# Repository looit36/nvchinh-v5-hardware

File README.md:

# MiniChinh - Micromouse Robot Controller Board

Dự án thiết kế mạch điều khiển robot dò mê cung (Micromouse) sử dụng phần mềm **KiCad**. Mạch tích hợp vi điều khiển STM32F411 tốc độ cao, driver động cơ kép, cảm biến quán tính IMU 6 trục, cảm biến encoder từ tính và dàn cảm biến quang hồng ngoại (IR).

---

## Hình ảnh Mạch PCB (3D & 2D Layout)

### Phối cảnh 3D

| Mặt trên | Mặt dưới |
| :---: | :---: |
|  |  |

| F.Cu + Silk | B.Cu + Silk |
| :---: | :---: |
|  |  |

---

## Sơ đồ Nguyên lý

### 1. Sơ đồ khối chính

### 2. Sơ đồ mạch phát & thu hồng ngoại

---

## Thông số Kỹ thuật Phần cứng

| Thành phần | Chi tiết linh kiện | Chức năng |
| :--- | :--- | :--- |
| **Vi điều khiển (MCU)** | STM32F411CEU6 (UFQFPN-48) | ARM Cortex-M4 100MHz, 512KB Flash, 128KB SRAM |
| **Driver Động cơ** | TI DRV8833PW (HTSSOP-16) | Điều khiển 2 động cơ DC độc lập, dòng tối đa 1.5A/kênh |
| **Cảm biến góc (IMU)** | Bosch BMI160 (LGA-14) | Cảm biến gia tốc & con quay hồi chuyển 6 trục (SPI/I2C) |
| **Bộ mã hóa bánh xe (Encoder)** | 2x MT6701CT (SO-8) | Cảm biến góc từ tính độ chính xác cao cho 2 bánh xe |
| **Cảm biến khoảng cách / Mê cung** | 4x SFH4546 (IR LED) + 4x SFH300 (Phototransistor) | Đo khoảng cách các vách tường mê cung, lái bằng MOSFET AO3400A |
| **Mạch nguồn (Power)** | AMS1117-5.0 & TI TPS73633DBV | Ổn áp 5V và 3.3V Low-Dropout cấp nguồn ổn định cho MCU và cảm biến |
| **Giao tiếp lập trình** | Cổng SWD chuẩn (GND, 3V3, SWDIO, SWCLK) | Nạp và gỡ lỗi bằng ST-Link / J-Link |
| **Ngoại vi & UI** | 5x LED báo trạng thái SMD 0603, 2x nút nhấn, 1x công tắc nguồn MSK12C02 | Giao diện tương tác và chọn chế độ chạy |

---

## Cấu trúc Thư mục

```text
minichinh/
├── minichinh.kicad_pro       # File dự án KiCad chính
├── minichinh.kicad_sch       # Sơ đồ nguyên lý chính
├── iremitter.kicad_sch       # Sơ đồ nguyên lý khối IR Emitter
├── minichinh.kicad_pcb       # Bản vẽ thiết kế mạch in PCB
├── fp-lib-table              # Bảng thư viện footprint
├── mouse.pretty/             # Thư viện footprint tùy chỉnh cho robot
├── minichinh.csv             # Danh sách bảng linh kiện (BOM)
├── geber/                    # Bộ file Gerber sẵn sàng để đặt mạch gia công
├── images/                   # Hình ảnh sơ đồ schematic và render 3D / 2D PCB
│   ├── minichinh.svg
│   ├── minichinh_ir_emitter.svg
│   ├── minichinh_schematic.pdf
│   ├── pcb_3d_top.png
│   ├── pcb_3d_bottom.png
│   ├── pcb_3d_iso.png
│   ├── pcb_top_layout.svg
│   └── pcb_bottom_layout.svg
└── README.md                 # Tài liệu giới thiệu dự án
```

---

## Hướng dẫn Sử dụng

1. **Mở dự án:**
   - Cài đặt KiCad phiên bản 8.0 hoặc 9.0 trở lên.
   - Mở file `minichinh.kicad_pro` để truy cập sơ đồ nguyên lý và layout PCB.
2. **Gia công mạch (PCB Manufacturing):**
   - Bộ file Gerber nén và đầy đủ các lớp đã được tạo sẵn trong thư mục [`geber/`](geber/). Có thể gửi trực tiếp cho các nhà sản xuất PCB (JLCPCB, PCBWay, v.v.).

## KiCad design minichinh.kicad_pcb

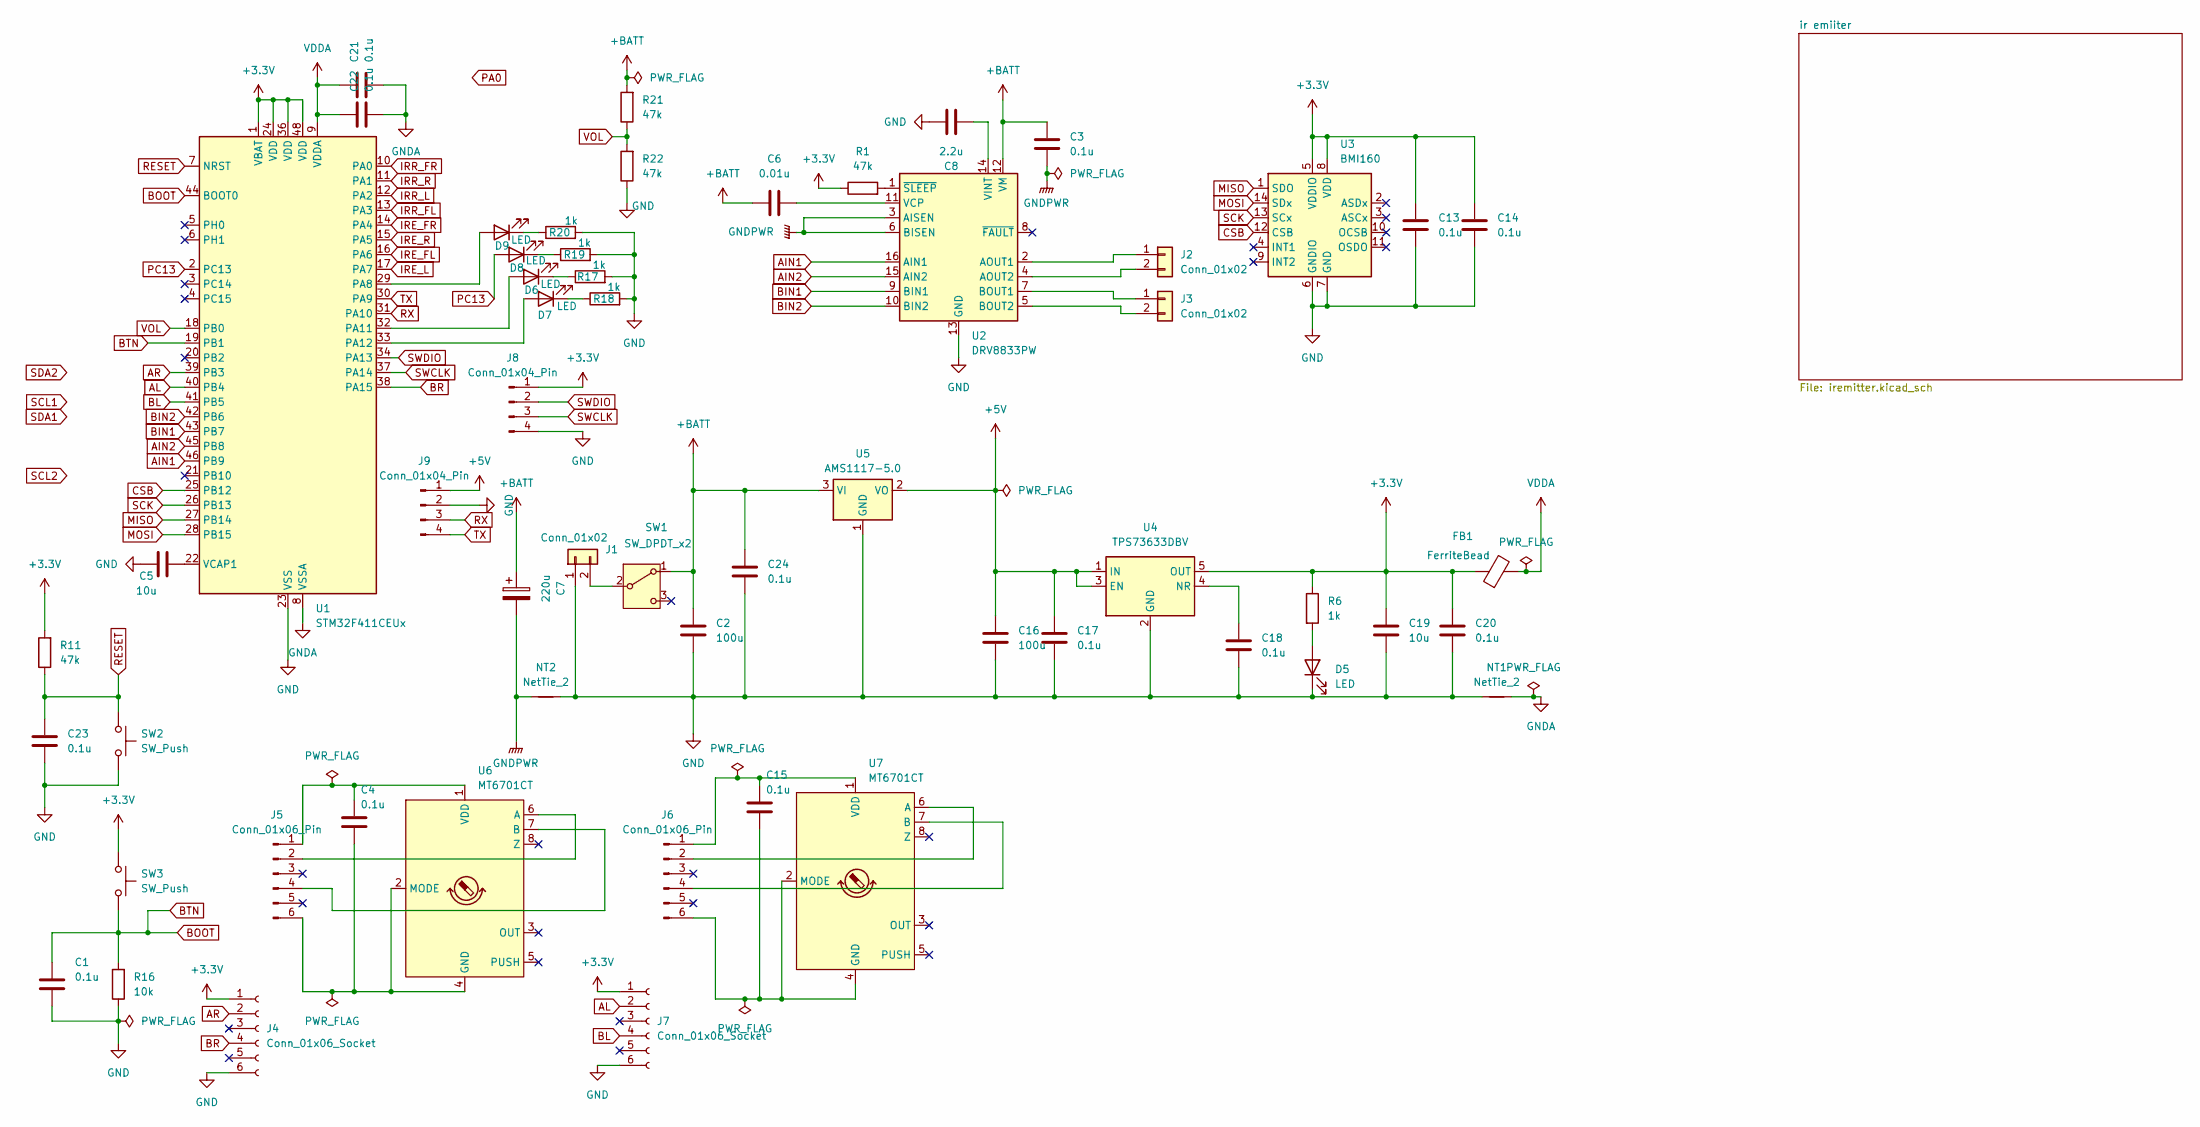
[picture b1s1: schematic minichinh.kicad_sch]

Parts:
C1, C21, C22, C23: 0.1u; C_0603_1608Metric
C2, C16: 100u; C_1210_3225Metric_Pad1.33x2.70mm_HandSolder
C3, C4, C13, C14, C15, C17, C18, C20, C24: 0.1u; C_0603_1608Metric_Pad1.08x0.95mm_HandSolder
C5: 10u; C_0603_1608Metric
C6: 0.01u; C_0603_1608Metric_Pad1.08x0.95mm_HandSolder
C7: 220u; CP_EIA-7343-31_Kemet-D_HandSolder
C8: 2.2u; C_0603_1608Metric_Pad1.08x0.95mm_HandSolder
C19: 10u; C_0603_1608Metric_Pad1.08x0.95mm_HandSolder
D5, D6, D7, D8, D9: LED; LED_0603_1608Metric_Pad1.05x0.95mm_HandSolder
FB1: FerriteBead; L_0805_2012Metric_Pad1.05x1.20mm_HandSolder
J1: Conn_01x02; JST_PH_B2B-PH-K_1x02_P2.00mm_Vertical
J2, J3: Conn_01x02; PinHeader_1x02_P2.54mm_Vertical
J4, J7: Conn_01x06_Socket; STAND_HOST_06
J5, J6: Conn_01x06_Pin; STAND_SLAVE_06
J8: Conn_01x04_Pin; PinHeader_2x02_P2.54mm_Vertical
J9: Conn_01x04_Pin; PinSocket_1x04_P2.54mm_Vertical
NT1: NetTie_2; NetTie-2_SMD_Pad0.5mm
NT2: NetTie_2; NetTie-2_SMD_Pad2.0mm
R1, R11, R21, R22: 47k; R_0603_1608Metric_Pad0.98x0.95mm_HandSolder
R6, R17, R18, R19, R20: 1k; R_0603_1608Metric_Pad0.98x0.95mm_HandSolder
R16: 10k; R_0603_1608Metric_Pad0.98x0.95mm_HandSolder
SW1: SW_DPDT_x2; SW_SPDT_Shouhan_MSK12C02
SW2, SW3: SW_Push; SW_SPST_TS-1088-xR025
U1: STM32F411CEUx; QFN-48-1EP_7x7mm_P0.5mm_EP3.5x3.5mm
U2: DRV8833PW; HTSSOP-16-1EP_4.4x5mm_P0.65mm_EP3.4x5mm
U3: BMI160; Bosch_LGA-14_3x2.5mm_P0.5mm
U4: TPS73633DBV; SOT-23-5
U5: AMS1117-5.0; SOT-223-3_TabPin2
U6, U7: MT6701CT; SO-8_3.9x4.9mm_P1.27mm

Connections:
+3.3V: C13.2, C14.2, C19.1, C20.1, FB1.1, J4.1, J7.1, J8.1, R1.1, R6.1, R11.2, SW3.1, U1.1 (VBAT), U1.24 (VDD), U1.36 (VDD), U1.48 (VDD), U3.5 (VDDIO), U3.8 (VDD), U4.5 (OUT)
+5V: C16.1, C17.1, J9.1, U4.1 (IN), U4.3 (EN), U5.2 (VO); also elsewhere on the board
+BATT: C2.1, C3.1, C6.1, C7.1, C24.1, R21.2, SW1.1 (A), U2.12 (VM), U5.3 (VI)
AIN1: U1.46 (PB9), U2.16 (AIN1)
AIN2: U1.45 (PB8), U2.15 (AIN2)
AL: J7.2, U1.40 (PB4)
AR: J4.2, U1.39 (PB3)
BIN1: U1.43 (PB7), U2.9 (BIN1)
BIN2: U1.42 (PB6), U2.10 (BIN2)
BL: J7.4, U1.41 (PB5)
BOOT: C1.1, R16.2, SW3.2, U1.19 (PB1), U1.44 (BOOT0)
BR: J4.4, U1.38 (PA15)
CSB: U1.25 (PB12), U3.12 (CSB)
GND: C1.2, C2.2, C5.1, C8.2, C13.1, C14.1, C16.2, C17.2, C18.2, C19.2, C20.2, C23.2, C24.2, D5.1 (K), J1.1, J4.6, J7.6, J8.4, J9.2, NT1.1, NT2.2, R16.1, R17.2, R18.2, R19.2, R20.2, R22.1, SW2.2, U1.23 (VSS), U1.35 (VSS), U1.47 (VSS), U1.49 (VSS), U2.13 (GND), U3.6 (GNDIO), U3.7 (GND), U4.2 (GND), U5.1 (GND); also elsewhere on the board
GNDA: C21.2, C22.2, NT1.2, U1.8 (VSSA); also elsewhere on the board
GNDPWR: C3.2, C7.2, NT2.1, U2.3 (AISEN), U2.6 (BISEN)
IRE_FL: U1.16 (PA6); also elsewhere on the board
IRE_FR: U1.14 (PA4); also elsewhere on the board
IRE_L: U1.17 (PA7); also elsewhere on the board
IRE_R: U1.15 (PA5); also elsewhere on the board
IRR_FL: U1.13 (PA3); also elsewhere on the board
IRR_FR: U1.10 (PA0); also elsewhere on the board
IRR_L: U1.12 (PA2); also elsewhere on the board
IRR_R: U1.11 (PA1); also elsewhere on the board
MISO: U1.27 (PB14), U3.1 (SDO)
MOSI: U1.28 (PB15), U3.14 (SDx)
unnamed: D5.2 (A), R6.2
unnamed: D6.2 (A), U1.32 (PA11)
unnamed: D6.1 (K), R17.1
unnamed: D7.2 (A), U1.33 (PA12)
unnamed: D7.1 (K), R18.1
unnamed: D8.1 (K), R19.1
unnamed: D9.2 (A), U1.29 (PA8)
unnamed: D9.1 (K), R20.1
unnamed: J1.2, SW1.2 (B)
unnamed: J2.1, U2.2 (AOUT1)
unnamed: J2.2, U2.4 (AOUT2)
unnamed: J3.1, U2.7 (BOUT1)
unnamed: J3.2, U2.5 (BOUT2)
unnamed: C4.1, J5.1, U6.1 (VDD)
unnamed: J5.2, U6.6 (A)
unnamed: J5.4, U6.7 (B)
unnamed: C4.2, J5.6, U6.2 (MODE), U6.4 (GND)
unnamed: C15.1, J6.1, U7.1 (VDD)
unnamed: J6.2, U7.6 (A)
unnamed: J6.4, U7.7 (B)
unnamed: C15.2, J6.6, U7.2 (MODE), U7.4 (GND)
unnamed: C5.2, U1.22 (VCAP1)
unnamed: C6.2, U2.11 (VCP)
unnamed: C8.1, U2.14 (VINT)
unnamed: R1.2, U2.1 (~SLEEP)
unnamed: C18.1, U4.4 (NR)
PC13: D8.2 (A), U1.2 (PC13)
RESET: C23.1, R11.1, SW2.1, U1.7 (NRST)
RX: J9.3, U1.31 (PA10)
SCK: U1.26 (PB13), U3.13 (SCx)
SWCLK: J8.3, U1.37 (PA14)
SWDIO: J8.2, U1.34 (PA13)
TX: J9.4, U1.30 (PA9)
VDDA: C21.1, C22.1, FB1.2, U1.9 (VDDA); also elsewhere on the board
VOL: R21.1, R22.2, U1.18 (PB0)

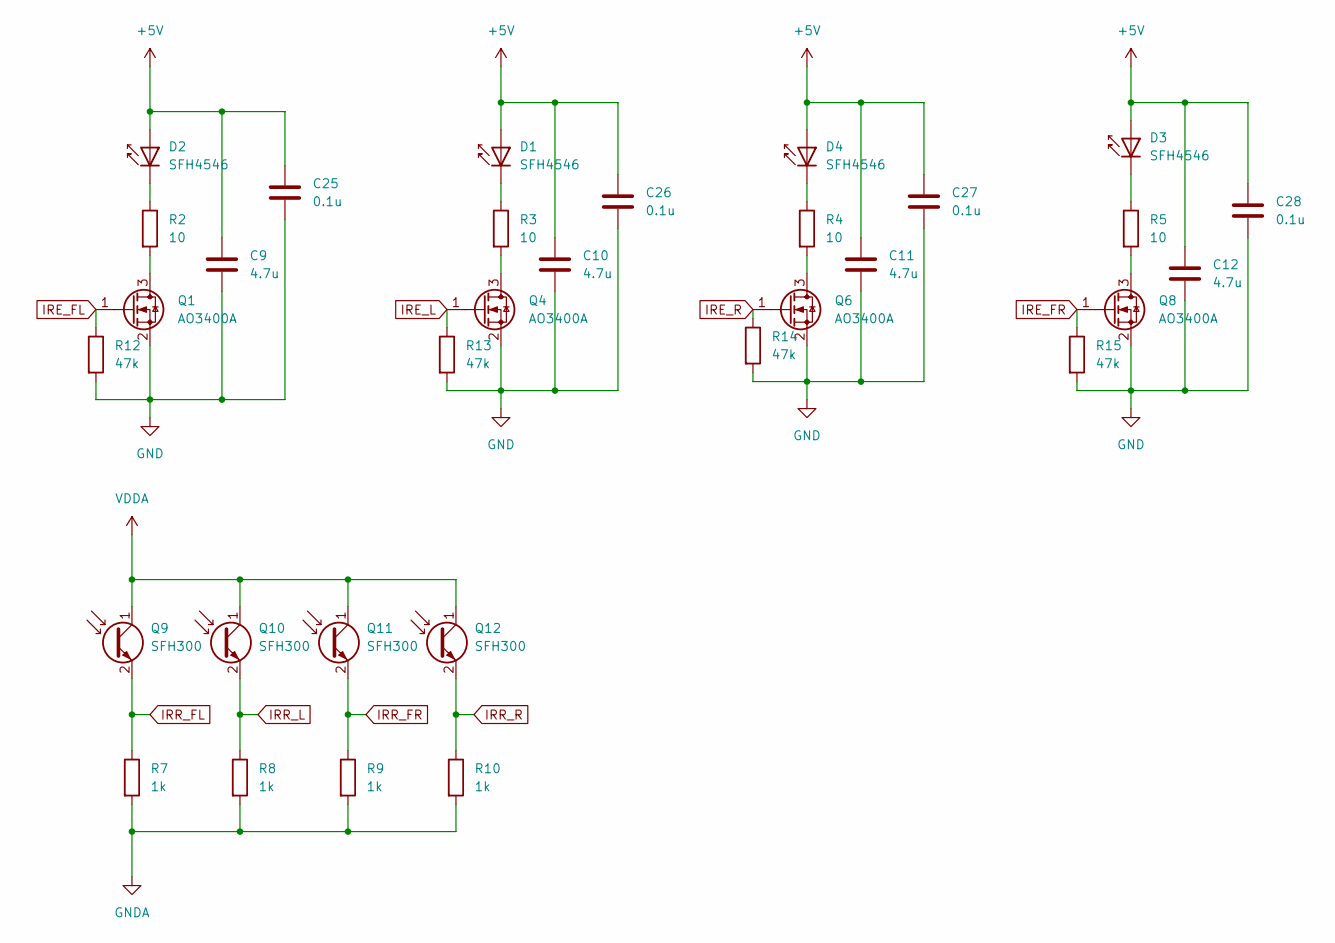
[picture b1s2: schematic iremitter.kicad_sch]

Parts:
C9, C10, C11, C12: 4.7u; C_0603_1608Metric_Pad1.08x0.95mm_HandSolder
C25, C26, C27, C28: 0.1u; C_0603_1608Metric_Pad1.08x0.95mm_HandSolder
D1, D2, D3, D4: SFH4546; LED_D5.0mm_Horizontal_O1.27mm_Z3.0mm_Clear
Q1, Q4, Q6, Q8: AO3400A; SOT-23
Q9, Q10, Q11, Q12: SFH300; LED_D3.0mm_Horizontal_O1.27mm_Z2.0mm_IRBlack
R2, R3, R4, R5: 10; R_0603_1608Metric_Pad0.98x0.95mm_HandSolder
R7, R8, R9, R10: 1k; R_0603_1608Metric_Pad0.98x0.95mm_HandSolder
R12, R13, R14, R15: 47k; R_0603_1608Metric_Pad0.98x0.95mm_HandSolder

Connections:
+5V: C9.1, C10.1, C11.1, C12.1, C25.1, C26.1, C27.1, C28.1, D1.2 (A), D2.2 (A), D3.2 (A), D4.2 (A); also elsewhere on the board
GND: C9.2, C10.2, C11.2, C12.2, C25.2, C26.2, C27.2, C28.2, Q1.2 (S), Q4.2 (S), Q6.2 (S), Q8.2 (S), R12.2, R13.2, R14.2, R15.2; also elsewhere on the board
GNDA: R7.2, R8.2, R9.2, R10.2; also elsewhere on the board
IRE_FL: Q1.1 (G), R12.1; also elsewhere on the board
IRE_FR: Q8.1 (G), R15.1; also elsewhere on the board
IRE_L: Q4.1 (G), R13.1; also elsewhere on the board
IRE_R: Q6.1 (G), R14.1; also elsewhere on the board
IRR_FL: Q9.2 (E), R7.1; also elsewhere on the board
IRR_FR: Q11.2 (E), R9.1; also elsewhere on the board
IRR_L: Q10.2 (E), R8.1; also elsewhere on the board
IRR_R: Q12.2 (E), R10.1; also elsewhere on the board
unnamed: D1.1 (K), R3.1
unnamed: D2.1 (K), R2.1
unnamed: D3.1 (K), R5.1
unnamed: D4.1 (K), R4.1
unnamed: Q1.3 (D), R2.2
unnamed: Q4.3 (D), R3.2
unnamed: Q6.3 (D), R4.2
unnamed: Q8.3 (D), R5.2
VDDA: Q9.1 (C), Q10.1 (C), Q11.1 (C), Q12.1 (C); also elsewhere on the board

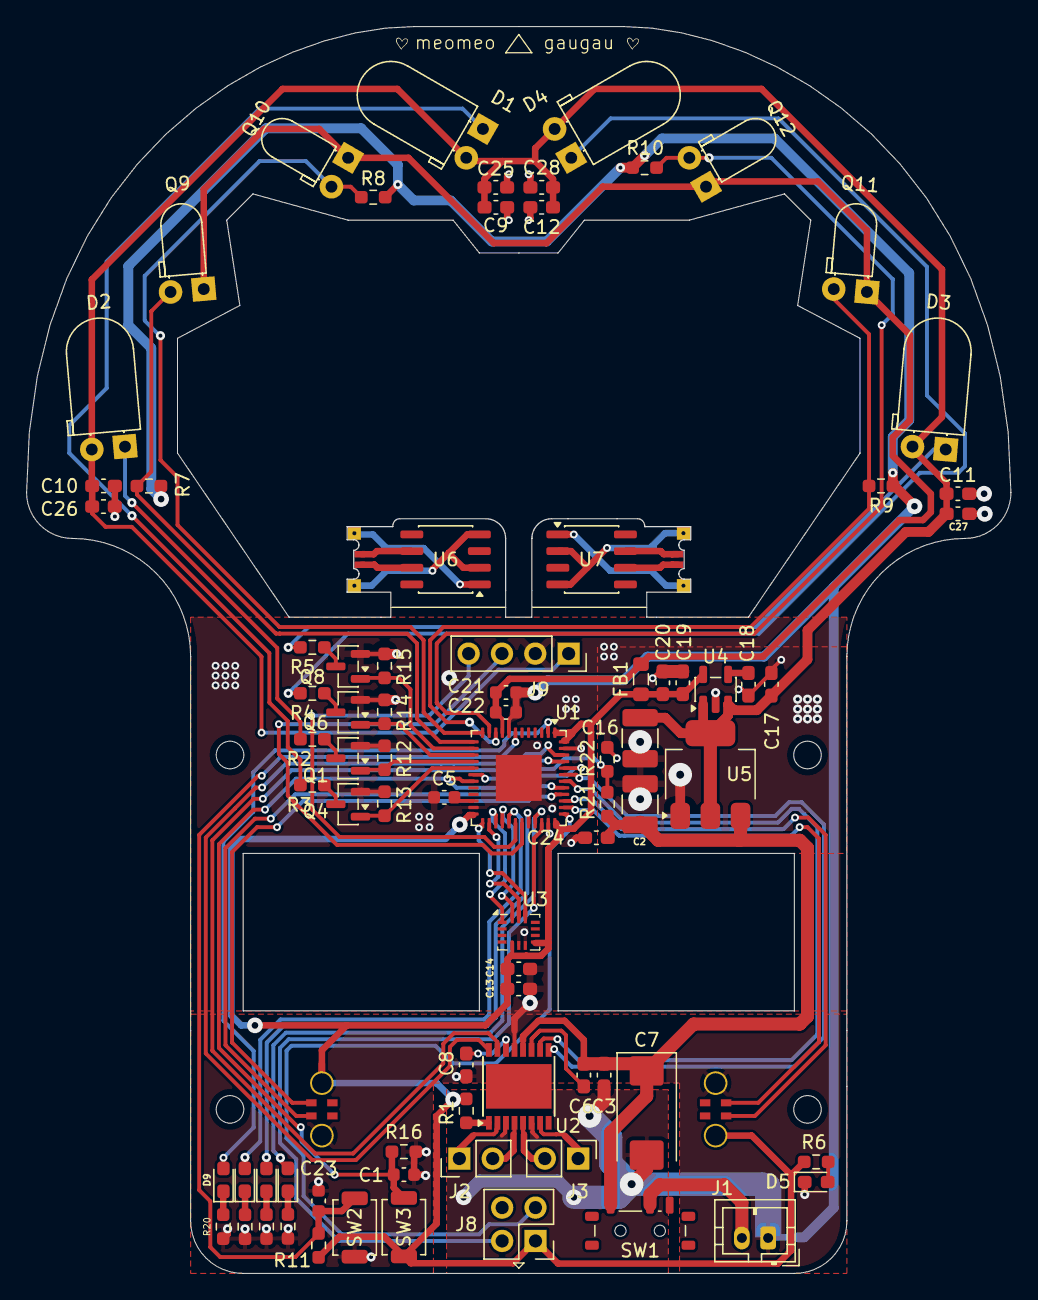
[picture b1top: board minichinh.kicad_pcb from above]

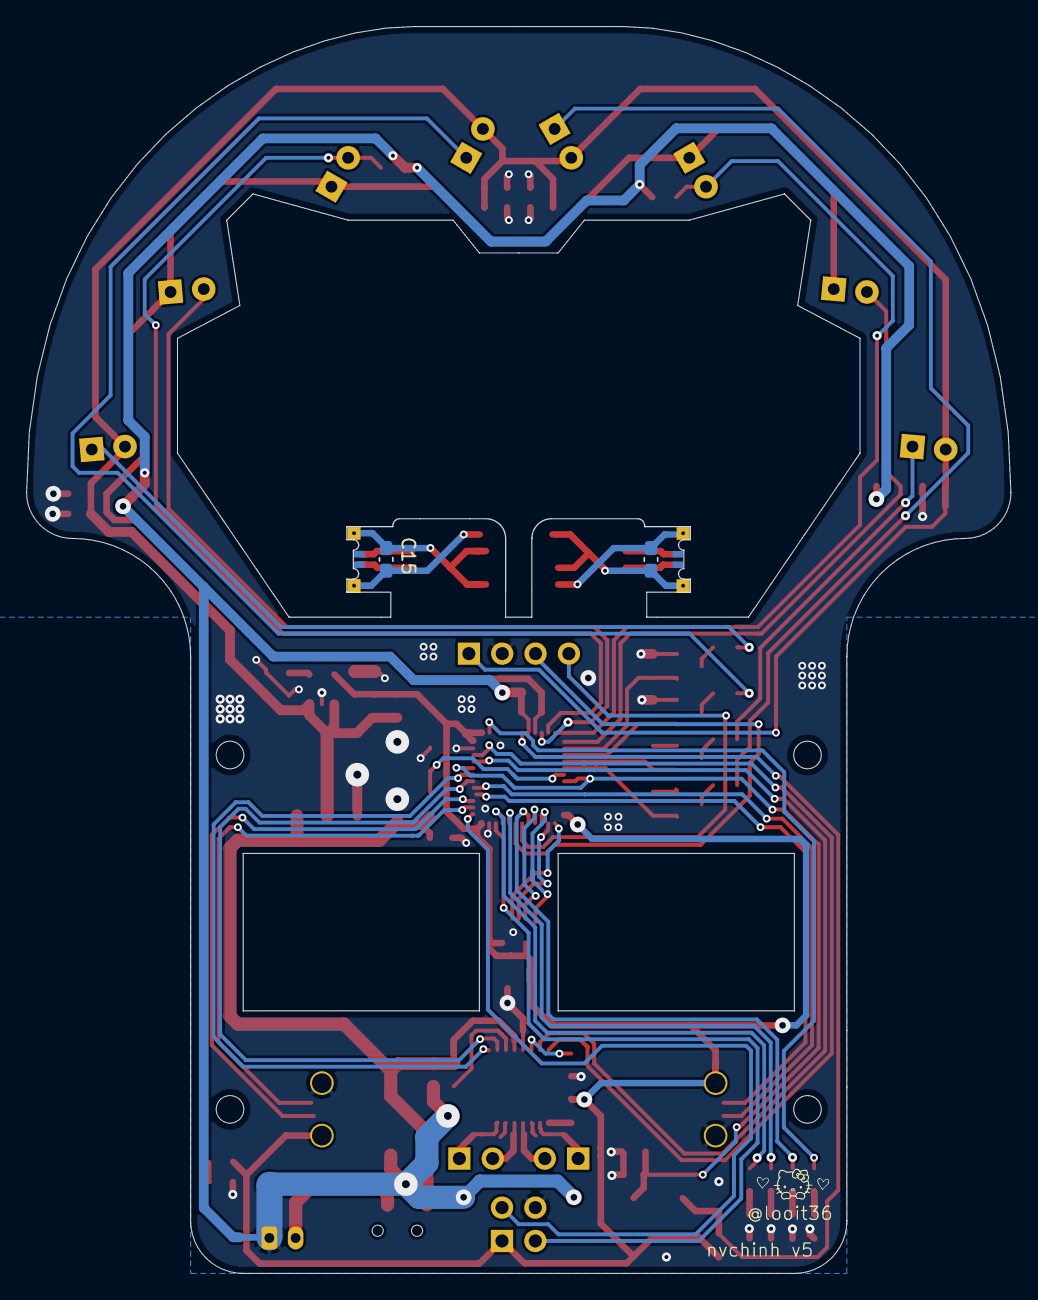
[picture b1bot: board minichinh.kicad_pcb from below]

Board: 2 copper layers, 75.0 x 95.0 mm, 89 parts (4 on the bottom side), 69 nets.
